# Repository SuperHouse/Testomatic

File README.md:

Testomatic PCB Test Jig System
==============================

Copyright 2024-2026 SuperHouse Automation Pty Ltd  [www.superhouse.tv]()

Testomatic is an open-source PCB test jig system with several goals:

1. Minimise reinvention when creating a test jig for a new **Device
Under Test (DUT)**.
2. Provide enough built-in I/O to **make the majority of tests easy**, with
expandability to **make harder tests possible**.
3. Allow the chassis to be quickly reused for multiple DUTs, with
each DUT having its own **Test Module**.
4. Integration with an **external test management / logging platform** for centralised storage of test results from one or more testers.

Testomatic is based around a Raspberry Pi, with a special PCB to provide additional I/O and protect the Pi from faults that may occur on the DUT. It uses removable Test Modules that provide the mechanical and electrical connection to each specific DUT. Currently we're using a simple Python testrunner script which has support for definition of multiple target boards, and can be controlled via the touchscreen using a control panel created using Node-RED Dashboard v2.

This is definitely a work in progress and the design is rapidly
developing. Most development and discussion of this project has taken
place on [SuperHouseTV livestreams](https://www.youtube.com/superhousetv) on YouTube, and on the [SuperHouse
Discord](https://www.superhouse.tv/discord/).

For an overview of how the project came to be and the design goals, see this 
presentation from Everything Open 2026:

The new v2 system is still in development and uses a vertically-mounted PCB with a card edge connector for bridging between the Raspberry Pi and the Test Module:

The v2.3 **Testomatic PCB**:

The **Testomatic PCB** fits into a laser-cut chassis with various other
parts:

**Test Modules** are built around a **Test Pin Carrier Board (TPCB)** which
uses a card edge connector commonly used for PCI to pass signals
between the Testomatic system and the test pins:

A reference design for the TPCB has been created as a starting point for making DUT-specific versions.

## Features
* 56 GPIOs grouped as 7 blocks, each with 8 pins.
* Each GPIO block can be configured for 3.3V or 5V I/O.
* Each GPIO pin can be digital input, digital output, 12-bit ADC, or 12-bit DAC.
* 4-port USB hub with all 4 ports passed up to the test module.
* SPI and I2C passed up to test module.
* Pi HAT EEPROM on Testomatic PCB for compliance with HAT automatic configuration.
* I2C EEPROM can be placed on Test Module to allow Testomatic to automatically identify which module is loaded.
* 5V power supply dedicated to Raspberry Pi independently of the DUT.
* 5V power supply with current sensing dedicated to DUT.
* 3V3 power supply with current sensing dedicated to DUT.
* VIN is passed to DUT with current sensing.
* Independent relay control of all 3 power rails to DUT.
* 1024 x 600 capacitive touchscreen.
* USB hub mounted in chassis for external connection of receipt printer, barcode scanner, keyboard, etc.
* Support for a 32-24 pixel thermal camera that can be mounted externally for capturing thermal images of the DUT.
* Support for an external button, such as a foot switch for control of test start.

## I/O Modules

Each block of 8 I/O pins is exposed on an I/O Module header, in 2mm pitch DIP format. This allows the use of different I/O modules to suit your needs. A generic I/O Module has been designed based on the AD5593R I2C I/O expander chip. Any pin on this module can be configured to be a digital input or output, analog input, or analog output.

Details of the module are available at [github.com/SuperHouse/IOMOD](https://github.com/SuperHouse/IOMOD)

The plan is to create other modules with different capabilities if required.

## Expansion
Simple tests can be done with the included I/O pins, but many DUTs will require more specific connections. Because the Test Module has SPI, I2C, and USB available, you can build your own custom circuitry directly into the Test Pin Carrier Board. This could include:

* USB-to-Serial converters
* CAN bus interfaces
* RS485 interfaces
* Dummy loads (either onboard or external)
* Light sensors
* Signal generators
* Programmable power supplies

To simplify this process for common tests, we have begun creating small modules that can be added quickly to the design of your Test Pin Carrier Board to save you doing this yourself. These modules include:

 * [USB-to-Serial / ESPFlasher](https://github.com/SuperHouse/ESPFMOD) (complete)
 * [CAN bus](https://github.com/SuperHouse/CANMOD) (complete)
 * [UPDI Programmer / Serial Module](https://github.com/SuperHouse/UPDIMOD)] (complete)

## LED Testing

Instead of relying on visual confirmation by an operator, Testomatic can use light sensors to 
validate correct operation of LEDs. These sensors can detect not only the level of illumination, 
but also the intensity at different wavelengths to verify that the correct colour of LED has 
been placed.

The "ColourSensor" directory contains Fusion design files and STLs for 30mm-long shrouds for 
mounting a VEML3328SL colour sensor, which in turn can be connected via I2C to the Testomatic. 

Designs are provided to suit 0603 LEDs in both straight and lateral orientations, and 3mm and 
5mm PTH LEDs.

The VEML3328SL can be carefully hand-soldered to the ends of thin wires connected to a JST-SH 
1mm connector for compatibility with Qwiic and Stemma, including breakout boards and multiplexers.

The VEML3328SL has a fixed I2C address of 0x10 so a common approach is to use a TCA9548A or 
PCA9546A I2C multiplexer to allow multiple colour sensors to be used.

## Testomatic Circuit Board Register

A closely related project is the Testomatic Circuit Board Register, which is software that 
provides a central location for storing production and testing data related to printed 
circuit board assembly (PCBA) services.

You can use Testomatic without the Register, and you can use the Register without Testomatic, 
but they are being developed in parallel with the intention that they complement each other 
and integrate smoothly.

Lean more about the Register at [github.com/SuperHouse/register](https://github.com/SuperHouse/register).

## Installation
Schematic and PCB were created in Fusion360 and exported as EAGLE format,
which can be imported back into Fusion360 or various other packages including KiCAD.

## Terminology
Chassis: A general purpose test jig that can execute tests.

Design: The abstract design of a type of printed circuit board, including the product name, SKU, schematic, PCB layout, bill of materials, and other production data.

Device: An assembled circuit board that is a concrete instantiation of a Design with an identifier such as a serial number that allows it to be unambiguously differentiated from other Devices of the same Design.

Device Under Test / DUT: When a Device is fitted into a Test Module in a Chassis so that it can be tested, it can be referred to as the Device Under Test.

Test Module: Hardware shim that fits into a Chassis and provides connections to a specific DUT.

Test Item: An abstract definition of an action that can be performed while testing a DUT, such as measurign a power rail, or sending a signal to it.

Test Step: An instantiation of a Test Item with specific configuration details such as which power rail to measure, or which I/O pin to use for sending a signal. Test Steps are executed automatically during the process of testing a DUT.

Manual Check: One step that is executed manually during the process of testing a DUT.

Test Suite: A collection of Test Items and Manual Checks that constitutes the steps required to test a DUT.

Test Run: One execution of a Test Suite against a Device Under Test.

Test Output: The data collected during a Test Run, with values and outcomes that are specific to that Device.

Test Result: Pass/Fail/Abort/Error. Pass: all Test Steps executed within required parameters. Fail: Test Suite was completed, but one or more Test Steps were outside required parameters. Abort: Test Suite was not completed because a Test Step caused the process to abort. Error: Test Suite was not completed because an environmental problem prevented execution.

Register: Software system that stores definitions of Designs, Test Items, and Test Suites, along with production data and Test Results related to Devices.

Test Suite Definition: A JSON file that contains the Test Steps and Manual Checks of a Test Suite.

Test Suite Package: A Test Suite Definition together with the additional artifacts it references and requires for execution, such as firmware binaries, whether delivered as a single archive or assembled from multiple sources such as separate API fetches.

Test Runner: Software that runs on the Chassis to load a Test Suite, execute its Test Steps against a Device, and report the resulting Test Results.

## Credits
Designed by Jonathan Oxer <jon@oxer.com.au> with the assistance of many members of the SuperHouse Discord.

## Distribution
The specific terms of distribution of this project are governed by the
license referenced below.

## License
Licensed under the TAPR Open Hardware License (www.tapr.org/OHL).
The "license" folder within this repository also contains a copy of
this license in plain text format.

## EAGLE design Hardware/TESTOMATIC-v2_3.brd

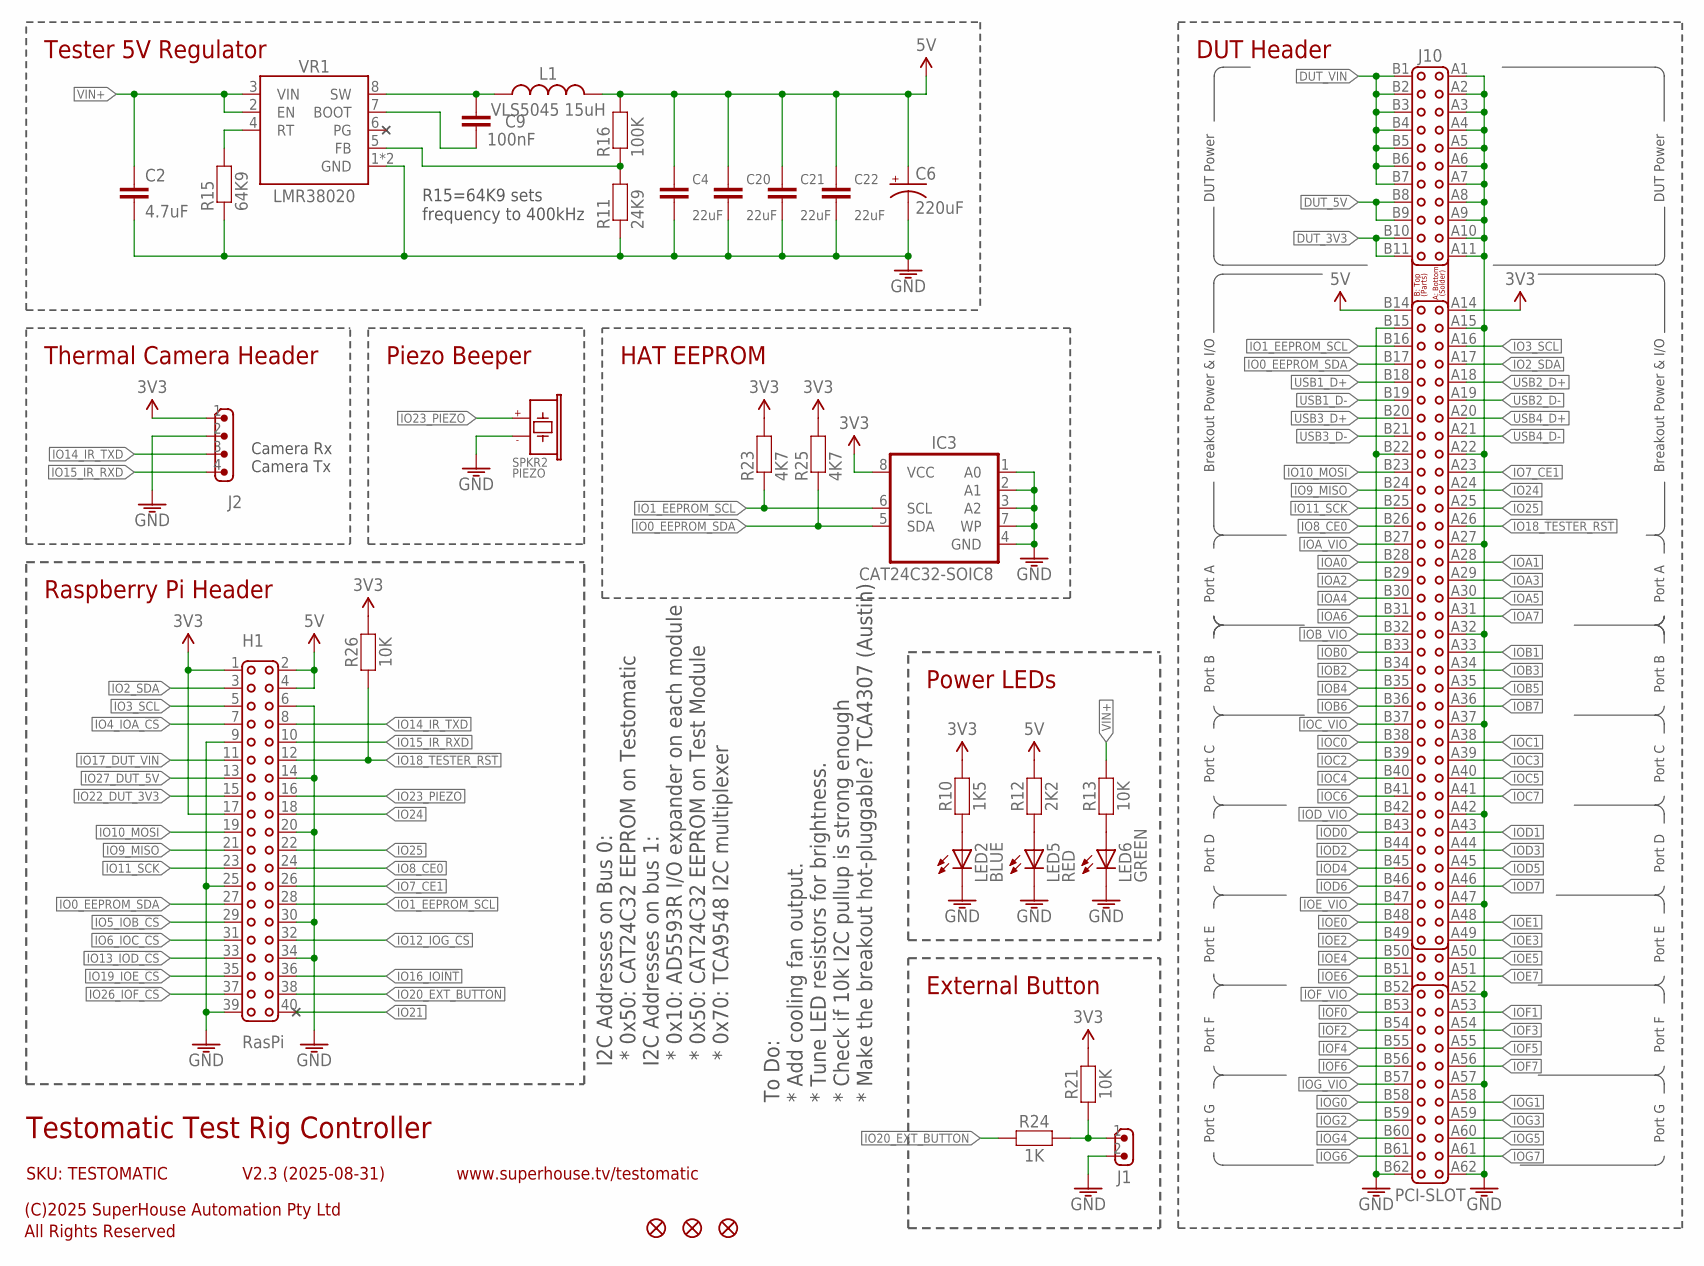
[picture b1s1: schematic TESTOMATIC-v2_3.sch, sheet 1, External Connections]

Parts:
C2: 4.7uF; C1206
C4, C20, C21, C22: 22uF; C0805
C6: 220uF; PANASONIC_G
C9: 100nF; C0603
FID1, FID2, FID3: FIDUCIAL1X2.5; FIDUCIAL-1X2.5
H1: RasPi; 2X20-P
IC3: CAT24C32-SOIC8; SOIC8
J1: M02-B2B-XH; JST-B2B-XH-A
J2: M04-B4B-XH; JST-B4B-XH-A
J10: PCI-SLOT
L1: VLS5045 15uH; INDUCTOR-5045
LED2: BLUE; LED-0603
LED5: RED; LED-0603
LED6: GREEN; LED-0603
R10: 1K5; R0603
R11: 24K9; R0603
R12: 2K2; R0603
R13, R21, R26: 10K; R0603
R15: 64K9; R0603
R16: 100K; R0603
R23, R25: 4K7; R0603
R24: 1K; R0603
SPKR2: PIEZO; PIEZO-9.6X9.6-SMT
VR1: LMR38020; HSOIC8

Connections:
3.3V: H1.1, H1.17, IC3.8 (VCC), J2.1, J10.A14, R10.2, R21.2, R23.2, R25.2, R26.2; also elsewhere on the board
5V: C4.1, C6.+, C20.1, C21.1, C22.1, H1.2, H1.4, J10.B14, L1.2, R12.2, R16.2; also elsewhere on the board
DUT_3V3: J10.B10, J10.B11; also elsewhere on the board
DUT_5V: J10.B8, J10.B9; also elsewhere on the board
DUT_VIN: J10.B1, J10.B2, J10.B3, J10.B4, J10.B5, J10.B6, J10.B7; also elsewhere on the board
GND: C2.2, C4.2, C6.-, C20.2, C21.2, C22.2, H1.6, H1.9, H1.14, H1.20, H1.25, H1.30, H1.34, H1.39, IC3.1 (A0), IC3.2 (A1), IC3.3 (A2), IC3.4 (GND), IC3.7 (WP), J1.2, J2.2, J10.A1, J10.A2, J10.A3, J10.A4, J10.A5, J10.A6, J10.A7, J10.A8, J10.A9, J10.A10, J10.A11, J10.A15, J10.A22, J10.A27, J10.A32, J10.A37, J10.A42, J10.A47, J10.A52, J10.A57, J10.A62, J10.B15, J10.B22, J10.B62, LED2.C, LED5.C, LED6.C, R11.1, R15.1, SPKR2.2 (-), VR1.1 (GND), VR1.TGND (GND); also elsewhere on the board
IO0_EEPROM_SDA: H1.27, IC3.5 (SDA), J10.B17, R25.1
IO1_EEPROM_SCL: H1.28, IC3.6 (SCL), J10.B16, R23.1
IO2_SDA: H1.3, J10.A17; also elsewhere on the board
IO3_SCL: H1.5, J10.A16; also elsewhere on the board
IO4_IOA_!CS: H1.7; also elsewhere on the board
IO5_IOB_!CS: H1.29; also elsewhere on the board
IO6_IOC_!CS: H1.31; also elsewhere on the board
IO7_CE1: H1.26, J10.A23
IO8_CE0: H1.24, J10.B26
IO9_MISO: H1.21, J10.B24; also elsewhere on the board
IO10_MOSI: H1.19, J10.B23; also elsewhere on the board
IO11_SCK: H1.23, J10.B25; also elsewhere on the board
IO12_IOG_!CS: H1.32; also elsewhere on the board
IO13_IOD_!CS: H1.33; also elsewhere on the board
IO14_IR_TXD: H1.8, J2.3
IO15_IR_RXD: H1.10, J2.4
IO16_IO!INT: H1.36; also elsewhere on the board
IO17_DUT_VIN: H1.11; also elsewhere on the board
IO18_!TESTER_RST: H1.12, J10.A26, R26.1; also elsewhere on the board
IO19_IOE_!CS: H1.35; also elsewhere on the board
IO20_EXT_BUTTON: H1.38, R24.1
IO21: H1.40
IO22_DUT_3V3: H1.15; also elsewhere on the board
IO23_PIEZO: H1.16, SPKR2.1 (+)
IO24: H1.18, J10.A24
IO25: H1.22, J10.A25
IO26_IOF_!CS: H1.37; also elsewhere on the board
IO27_DUT_5V: H1.13; also elsewhere on the board
IOA0: J10.B28; also elsewhere on the board
IOA1: J10.A28; also elsewhere on the board
IOA2: J10.B29; also elsewhere on the board
IOA3: J10.A29; also elsewhere on the board
IOA4: J10.B30; also elsewhere on the board
IOA5: J10.A30; also elsewhere on the board
IOA6: J10.B31; also elsewhere on the board
IOA7: J10.A31; also elsewhere on the board
IOA_VIO: J10.B27; also elsewhere on the board
IOB0: J10.B33; also elsewhere on the board
IOB1: J10.A33; also elsewhere on the board
IOB2: J10.B34; also elsewhere on the board
IOB3: J10.A34; also elsewhere on the board
IOB4: J10.B35; also elsewhere on the board
IOB5: J10.A35; also elsewhere on the board
IOB6: J10.B36; also elsewhere on the board
IOB7: J10.A36; also elsewhere on the board
IOB_VIO: J10.B32; also elsewhere on the board
IOC0: J10.B38; also elsewhere on the board
IOC1: J10.A38; also elsewhere on the board
IOC2: J10.B39; also elsewhere on the board
IOC3: J10.A39; also elsewhere on the board
IOC4: J10.B40; also elsewhere on the board
IOC5: J10.A40; also elsewhere on the board
IOC6: J10.B41; also elsewhere on the board
IOC7: J10.A41; also elsewhere on the board
IOC_VIO: J10.B37; also elsewhere on the board
IOD0: J10.B43; also elsewhere on the board
IOD1: J10.A43; also elsewhere on the board
IOD2: J10.B44; also elsewhere on the board
IOD3: J10.A44; also elsewhere on the board
IOD4: J10.B45; also elsewhere on the board
IOD5: J10.A45; also elsewhere on the board
IOD6: J10.B46; also elsewhere on the board
IOD7: J10.A46; also elsewhere on the board
IOD_VIO: J10.B42; also elsewhere on the board
IOE0: J10.B48; also elsewhere on the board
IOE1: J10.A48; also elsewhere on the board
IOE2: J10.B49; also elsewhere on the board
IOE3: J10.A49; also elsewhere on the board
IOE4: J10.B50; also elsewhere on the board
IOE5: J10.A50; also elsewhere on the board
IOE6: J10.B51; also elsewhere on the board
IOE7: J10.A51; also elsewhere on the board
IOE_VIO: J10.B47; also elsewhere on the board
IOF0: J10.B53; also elsewhere on the board
IOF1: J10.A53; also elsewhere on the board
IOF2: J10.B54; also elsewhere on the board
IOF3: J10.A54; also elsewhere on the board
IOF4: J10.B55; also elsewhere on the board
IOF5: J10.A55; also elsewhere on the board
IOF6: J10.B56; also elsewhere on the board
IOF7: J10.A56; also elsewhere on the board
IOF_VIO: J10.B52; also elsewhere on the board
IOG0: J10.B58; also elsewhere on the board
IOG1: J10.A58; also elsewhere on the board
IOG2: J10.B59; also elsewhere on the board
IOG3: J10.A59; also elsewhere on the board
IOG4: J10.B60; also elsewhere on the board
IOG5: J10.A60; also elsewhere on the board
IOG6: J10.B61; also elsewhere on the board
IOG7: J10.A61; also elsewhere on the board
IOG_VIO: J10.B57; also elsewhere on the board
unnamed: LED2.A, R10.1
unnamed: C9.1, L1.1, VR1.8 (SW)
unnamed: LED5.A, R12.1
unnamed: LED6.A, R13.1
unnamed: J1.1, R21.1, R24.2
unnamed: R15.2, VR1.4 (RT)
unnamed: R11.2, R16.1, VR1.5 (FB)
unnamed: C9.2, VR1.7 (BOOT)
PG: VR1.6 (PG); also elsewhere on the board
USB1_D+: J10.B18; also elsewhere on the board
USB1_D-: J10.B19; also elsewhere on the board
USB2_D+: J10.A18; also elsewhere on the board
USB2_D-: J10.A19; also elsewhere on the board
USB3_D+: J10.B20; also elsewhere on the board
USB3_D-: J10.B21; also elsewhere on the board
USB4_D+: J10.A20; also elsewhere on the board
USB4_D-: J10.A21; also elsewhere on the board
VIN+: C2.1, R13.2, VR1.2 (EN), VR1.3 (VIN); also elsewhere on the board

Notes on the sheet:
Testomatic Test Rig Controller
V2.3 (2025-08-31)
SKU: TESTOMATIC
(C)2025 SuperHouse Automation Pty Ltd
All Rights Reserved
www.superhouse.tv/testomatic
Tester 5V Regulator
R15=64K9 sets frequency to 400kHz
To Do: * Add cooling fan output. * Tune LED resistors for brightness. * Check if 10k I2C pullup is strong enough * Make the breakout hot-pluggable? TCA4307 (Austin)
Raspberry Pi Header
Thermal Camera Header
Camera Rx
Camera Tx
DUT Header
Piezo Beeper
DUT Power
Breakout Power & I/O
Port D
Power LEDs
External Button
HAT EEPROM
Port E
Port F
Port G
Port C
Port B
Port A
I2C Addresses on Bus 0: * 0x50: CAT24C32 EEPROM on Testomatic I2C Addresses on bus 1: * 0x10: AD5593R I/O expander on each module * 0x50: CAT24C32 EEPROM on Test Module * 0x70: TCA9548 I2C multiplexer

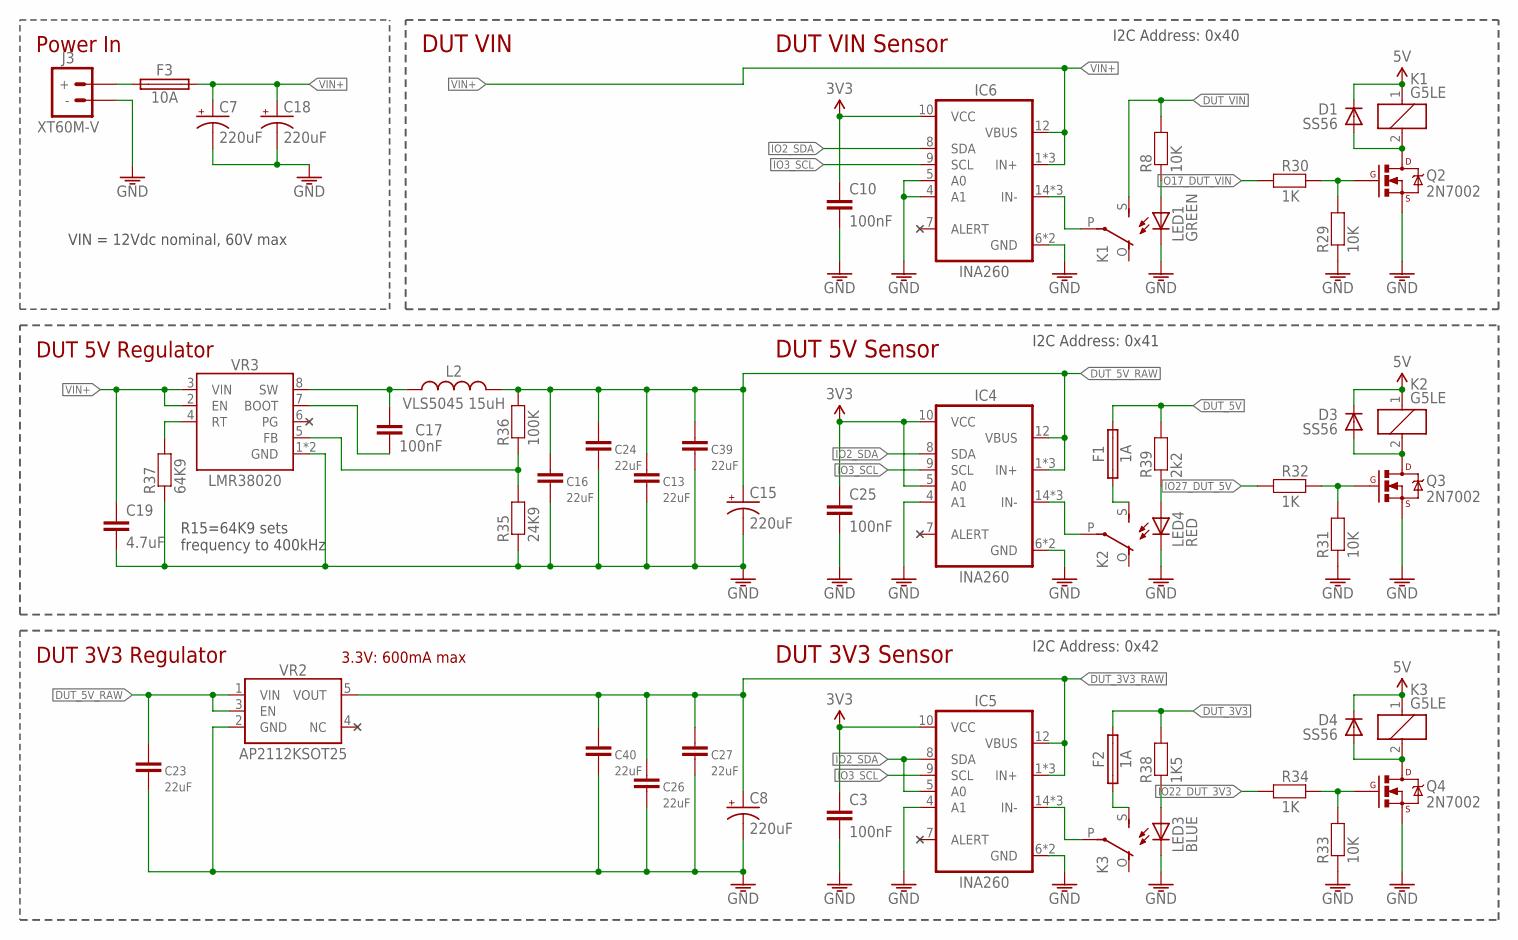
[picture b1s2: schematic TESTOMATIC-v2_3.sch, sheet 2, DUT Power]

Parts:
C3, C10, C17, C25: 100nF; C0603
C7, C8, C15, C18: 220uF; PANASONIC_G
C13, C16, C23, C24, C26, C27, C39, C40: 22uF; C0805
C19: 4.7uF; C1206
D1, D3, D4: SS56; SMA-DIODE
F1, F2: 1A; 1206
F3: 10A; MCCQ-122
IC4, IC5, IC6: INA260; TSSOP-16
J3: XT60M-V; XT60PW-M-V
K1, K2, K3: G5LE
L2: VLS5045 15uH; INDUCTOR-5045
LED1: GREEN; LED-0603
LED3: BLUE; LED-0603
LED4: RED; LED-0603
Q2, Q3, Q4: 2N7002; SOT23-3
R8, R29, R31, R33: 10K; R0603
R30, R32, R34: 1K; R0603
R35: 24K9; R0603
R36: 100K; R0603
R37: 64K9; R0603
R38: 1K5; R0603
R39: 2k2; R0603
VR2: AP2112KSOT25; SOT23-5
VR3: LMR38020; HSOIC8

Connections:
3.3V: C3.1, C10.1, C25.1, IC4.5 (A0), IC4.10 (VCC), IC5.10 (VCC), IC6.10 (VCC); also elsewhere on the board
5V: D1.C, D3.C, D4.C, K1.1, K2.1, K3.1; also elsewhere on the board
DUT_3V3: F2.2, R38.2; also elsewhere on the board
DUT_3V3_RAW: C8.+, C26.1, C27.1, C40.1, IC5.1 (IN+), IC5.2 (IN+), IC5.3 (IN+), IC5.12 (VBUS), VR2.5 (VOUT)
DUT_5V: F1.2, R39.2; also elsewhere on the board
DUT_5V_RAW: C13.1, C15.+, C16.1, C23.1, C24.1, C39.1, IC4.1 (IN+), IC4.2 (IN+), IC4.3 (IN+), IC4.12 (VBUS), L2.2, R36.2, VR2.1 (VIN), VR2.3 (EN)
DUT_VIN: K1.S (NO), R8.2; also elsewhere on the board
GND: C3.2, C7.-, C8.-, C10.2, C13.2, C15.-, C16.2, C18.-, C19.2, C23.2, C24.2, C25.2, C26.2, C27.2, C39.2, C40.2, IC4.4 (A1), IC4.6 (GND), IC4.11 (GND), IC5.4 (A1), IC5.6 (GND), IC5.11 (GND), IC6.4 (A1), IC6.5 (A0), IC6.6 (GND), IC6.11 (GND), J3.-, LED1.C, LED3.C, LED4.C, Q2.2 (S), Q3.2 (S), Q4.2 (S), R29.1, R31.1, R33.1, R35.1, R37.1, VR2.2 (GND), VR3.1 (GND), VR3.TGND (GND); also elsewhere on the board
IO2_SDA: IC4.8 (SDA), IC5.5 (A0), IC5.8 (SDA), IC6.8 (SDA); also elsewhere on the board
IO3_SCL: IC4.9 (SCL), IC5.9 (SCL), IC6.9 (SCL); also elsewhere on the board
IO17_DUT_VIN: R30.1; also elsewhere on the board
IO22_DUT_3V3: R34.1; also elsewhere on the board
IO27_DUT_5V: R32.1; also elsewhere on the board
unnamed: F3.1, F3.2 (1), J3.+
unnamed: D4.A, K3.2, Q4.3 (D)
unnamed: IC4.14 (IN-), IC4.15 (IN-), IC4.16 (IN-), K2.P (COM)
unnamed: IC6.14 (IN-), IC6.15 (IN-), IC6.16 (IN-), K1.P (COM)
unnamed: D1.A, K1.2, Q2.3 (D)
unnamed: LED1.A, R8.1
unnamed: Q2.1 (G), R29.2, R30.2
unnamed: F2.1, K3.S (NO)
unnamed: F1.1, K2.S (NO)
unnamed: D3.A, K2.2, Q3.3 (D)
unnamed: Q3.1 (G), R31.2, R32.2
unnamed: Q4.1 (G), R33.2, R34.2
unnamed: IC5.14 (IN-), IC5.15 (IN-), IC5.16 (IN-), K3.P (COM)
unnamed: C17.1, L2.1, VR3.8 (SW)
unnamed: R37.2, VR3.4 (RT)
unnamed: R35.2, R36.1, VR3.5 (FB)
unnamed: C17.2, VR3.7 (BOOT)
unnamed: LED4.A, R39.1
unnamed: LED3.A, R38.1
PG: VR3.6 (PG); also elsewhere on the board
VIN+: C7.+, C18.+, C19.1, F3.3 (2), F3.4 (2), IC6.1 (IN+), IC6.2 (IN+), IC6.3 (IN+), IC6.12 (VBUS), VR3.2 (EN), VR3.3 (VIN); also elsewhere on the board

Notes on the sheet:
DUT VIN Sensor
I2C Address: 0x40
DUT 5V Sensor
I2C Address: 0x41
DUT 3V3 Sensor
I2C Address: 0x42
3.3V: 600mA max
DUT 3V3 Regulator
DUT 5V Regulator
R15=64K9 sets frequency to 400kHz
DUT VIN
VIN = 12Vdc nominal, 60V max
Power In

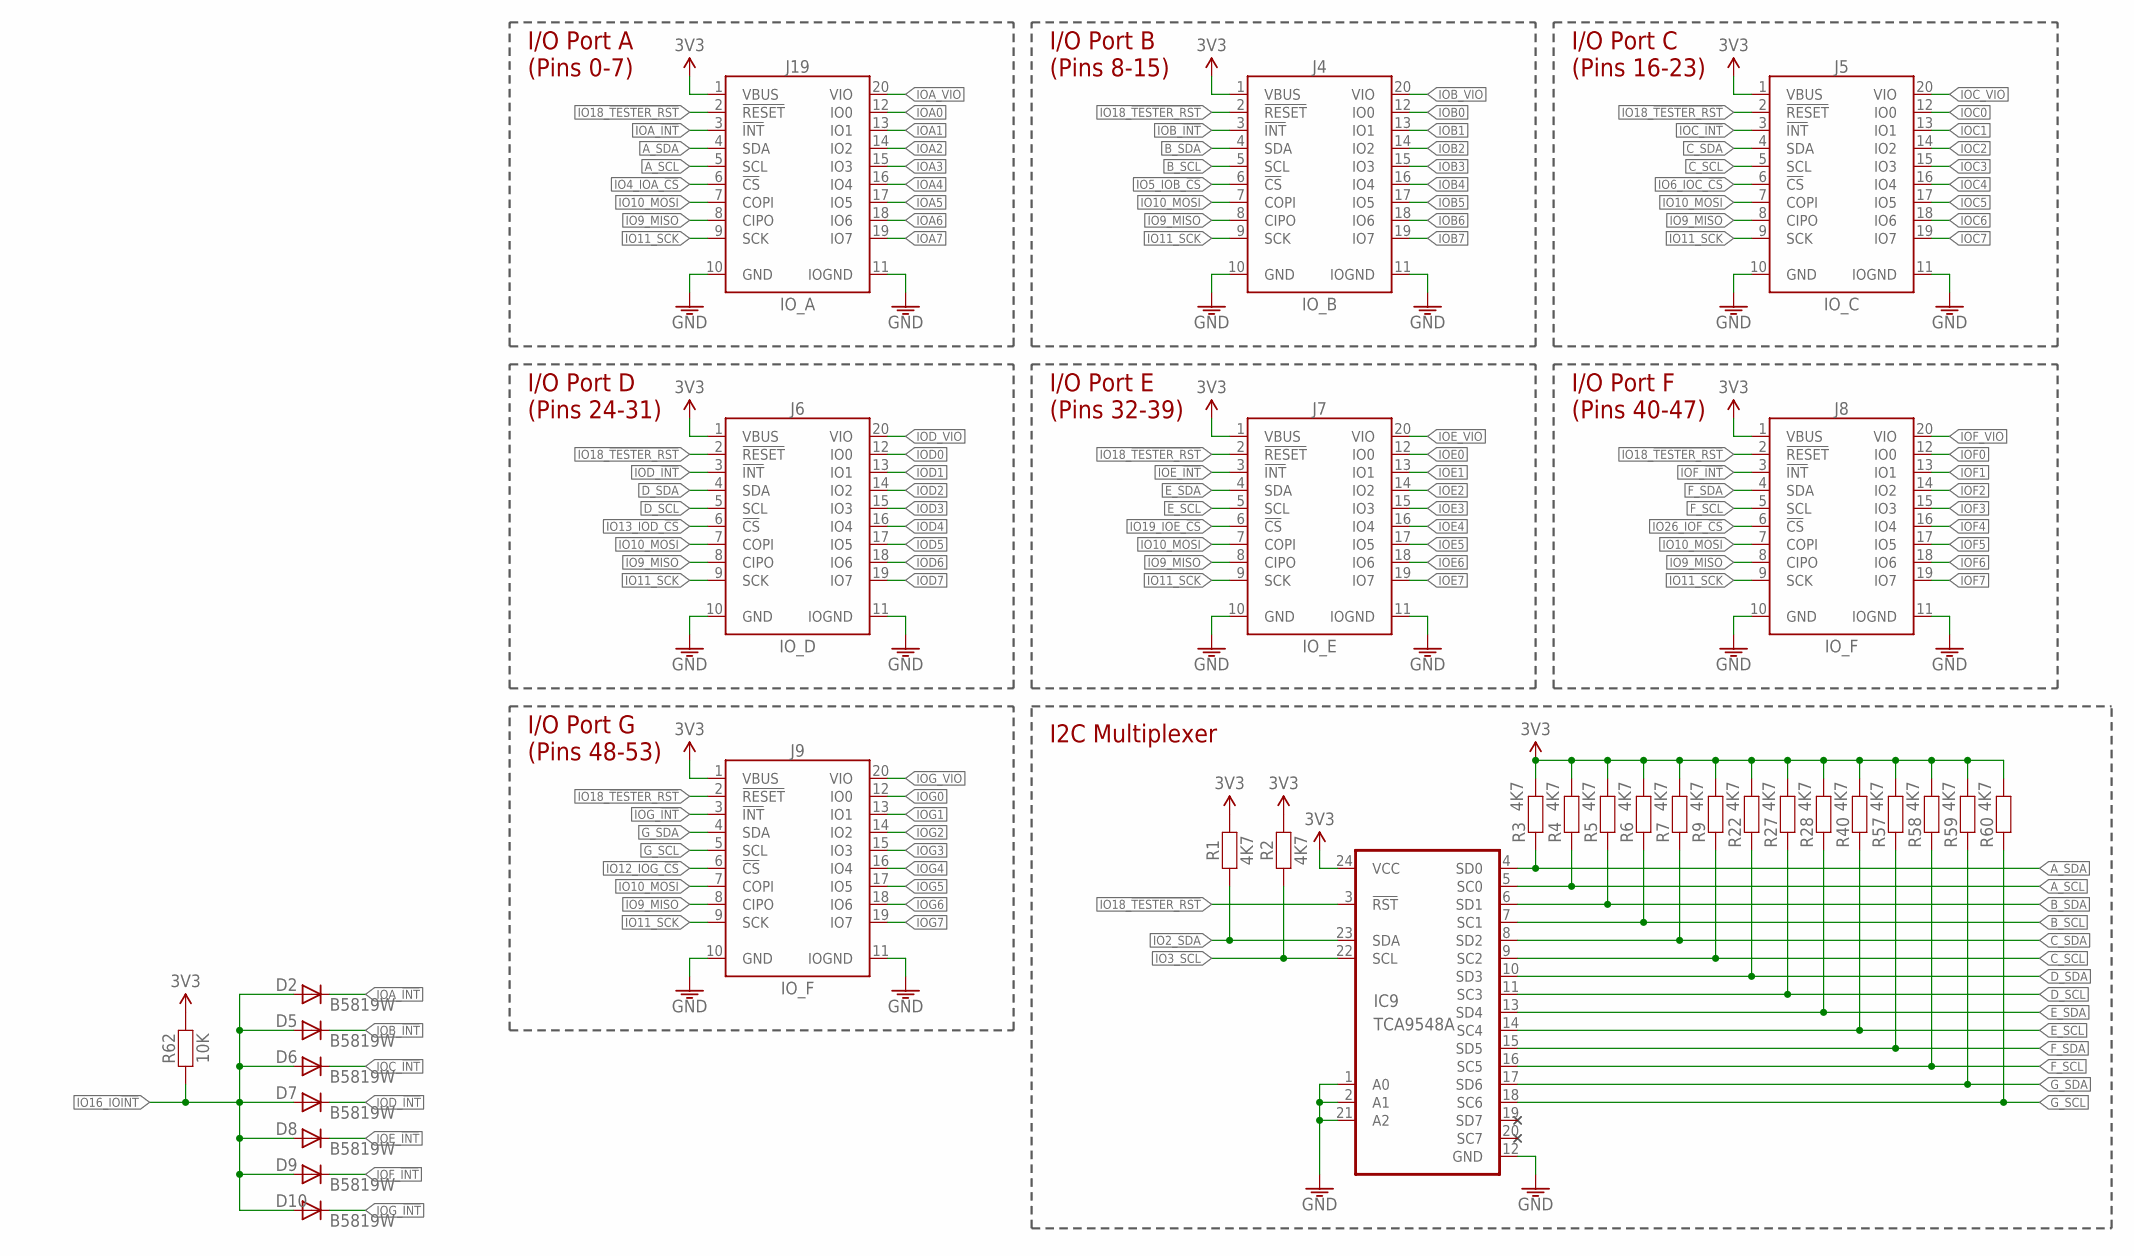
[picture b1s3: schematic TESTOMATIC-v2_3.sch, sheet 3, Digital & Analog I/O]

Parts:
D2, D5, D6, D7, D8, D9, D10: B5819W; SOD-123
IC9: TCA9548A; TSSOP24
J4: IO_B; IOMOD
J5: IO_C; IOMOD
J6: IO_D; IOMOD
J7: IO_E; IOMOD
J8, J9: IO_F; IOMOD
J19: IO_A; IOMOD
R1, R2, R3, R4, R5, R6, R7, R9, R22, R27, R28, R40, R57, R58, R59, R60: 4K7; R0603
R62: 10K; R0603

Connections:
3.3V: IC9.24 (VCC), J4.1 (VBUS), J5.1 (VBUS), J6.1 (VBUS), J7.1 (VBUS), J8.1 (VBUS), J9.1 (VBUS), J19.1 (VBUS), R1.2, R2.2, R3.2, R4.2, R5.2, R6.2, R7.2, R9.2, R22.2, R27.2, R28.2, R40.2, R57.2, R58.2, R59.2, R60.2, R62.2; also elsewhere on the board
A_SCL: IC9.5 (SC0), J19.5 (SCL), R4.1
A_SDA: IC9.4 (SD0), J19.4 (SDA), R3.1
B_SCL: IC9.7 (SC1), J4.5 (SCL), R6.1
B_SDA: IC9.6 (SD1), J4.4 (SDA), R5.1
C_SCL: IC9.9 (SC2), J5.5 (SCL), R9.1
C_SDA: IC9.8 (SD2), J5.4 (SDA), R7.1
D_SCL: IC9.11 (SC3), J6.5 (SCL), R27.1
D_SDA: IC9.10 (SD3), J6.4 (SDA), R22.1
E_SCL: IC9.14 (SC4), J7.5 (SCL), R40.1
E_SDA: IC9.13 (SD4), J7.4 (SDA), R28.1
F_SCL: IC9.16 (SC5), J8.5 (SCL), R58.1
F_SDA: IC9.15 (SD5), J8.4 (SDA), R57.1
GND: IC9.1 (A0), IC9.2 (A1), IC9.12 (GND), IC9.21 (A2), J4.10 (GND), J4.11 (IOGND), J5.10 (GND), J5.11 (IOGND), J6.10 (GND), J6.11 (IOGND), J7.10 (GND), J7.11 (IOGND), J8.10 (GND), J8.11 (IOGND), J9.10 (GND), J9.11 (IOGND), J19.10 (GND), J19.11 (IOGND); also elsewhere on the board
G_SCL: IC9.18 (SC6), J9.5 (SCL), R60.1
G_SDA: IC9.17 (SD6), J9.4 (SDA), R59.1
IO2_SDA: IC9.23 (SDA), R1.1; also elsewhere on the board
IO3_SCL: IC9.22 (SCL), R2.1; also elsewhere on the board
IO4_IOA_!CS: J19.6 (!CS); also elsewhere on the board
IO5_IOB_!CS: J4.6 (!CS); also elsewhere on the board
IO6_IOC_!CS: J5.6 (!CS); also elsewhere on the board
IO9_MISO: J4.8 (CIPO), J5.8 (CIPO), J6.8 (CIPO), J7.8 (CIPO), J8.8 (CIPO), J9.8 (CIPO), J19.8 (CIPO); also elsewhere on the board
IO10_MOSI: J4.7 (COPI), J5.7 (COPI), J6.7 (COPI), J7.7 (COPI), J8.7 (COPI), J9.7 (COPI), J19.7 (COPI); also elsewhere on the board
IO11_SCK: J4.9 (SCK), J5.9 (SCK), J6.9 (SCK), J7.9 (SCK), J8.9 (SCK), J9.9 (SCK), J19.9 (SCK); also elsewhere on the board
IO12_IOG_!CS: J9.6 (!CS); also elsewhere on the board
IO13_IOD_!CS: J6.6 (!CS); also elsewhere on the board
IO16_IO!INT: D2.2 (A), D5.2 (A), D6.2 (A), D7.2 (A), D8.2 (A), D9.2 (A), D10.2 (A), R62.1; also elsewhere on the board
IO18_!TESTER_RST: IC9.3 (!RST), J4.2 (!RESET), J5.2 (!RESET), J6.2 (!RESET), J7.2 (!RESET), J8.2 (!RESET), J9.2 (!RESET), J19.2 (!RESET); also elsewhere on the board
IO19_IOE_!CS: J7.6 (!CS); also elsewhere on the board
IO26_IOF_!CS: J8.6 (!CS); also elsewhere on the board
IOA0: J19.12 (IO0); also elsewhere on the board
IOA1: J19.13 (IO1); also elsewhere on the board
IOA2: J19.14 (IO2); also elsewhere on the board
IOA3: J19.15 (IO3); also elsewhere on the board
IOA4: J19.16 (IO4); also elsewhere on the board
IOA5: J19.17 (IO5); also elsewhere on the board
IOA6: J19.18 (IO6); also elsewhere on the board
IOA7: J19.19 (IO7); also elsewhere on the board
IOA_!INT: D2.1 (C), J19.3 (!INT)
IOA_VIO: J19.20 (VIO); also elsewhere on the board
IOB0: J4.12 (IO0); also elsewhere on the board
IOB1: J4.13 (IO1); also elsewhere on the board
IOB2: J4.14 (IO2); also elsewhere on the board
IOB3: J4.15 (IO3); also elsewhere on the board
IOB4: J4.16 (IO4); also elsewhere on the board
IOB5: J4.17 (IO5); also elsewhere on the board
IOB6: J4.18 (IO6); also elsewhere on the board
IOB7: J4.19 (IO7); also elsewhere on the board
IOB_!INT: D5.1 (C), J4.3 (!INT)
IOB_VIO: J4.20 (VIO); also elsewhere on the board
IOC0: J5.12 (IO0); also elsewhere on the board
IOC1: J5.13 (IO1); also elsewhere on the board
IOC2: J5.14 (IO2); also elsewhere on the board
IOC3: J5.15 (IO3); also elsewhere on the board
IOC4: J5.16 (IO4); also elsewhere on the board
IOC5: J5.17 (IO5); also elsewhere on the board
IOC6: J5.18 (IO6); also elsewhere on the board
IOC7: J5.19 (IO7); also elsewhere on the board
IOC_!INT: D6.1 (C), J5.3 (!INT)
IOC_VIO: J5.20 (VIO); also elsewhere on the board
IOD0: J6.12 (IO0); also elsewhere on the board
IOD1: J6.13 (IO1); also elsewhere on the board
IOD2: J6.14 (IO2); also elsewhere on the board
IOD3: J6.15 (IO3); also elsewhere on the board
IOD4: J6.16 (IO4); also elsewhere on the board
IOD5: J6.17 (IO5); also elsewhere on the board
IOD6: J6.18 (IO6); also elsewhere on the board
IOD7: J6.19 (IO7); also elsewhere on the board
IOD_!INT: D7.1 (C), J6.3 (!INT)
IOD_VIO: J6.20 (VIO); also elsewhere on the board
IOE0: J7.12 (IO0); also elsewhere on the board
IOE1: J7.13 (IO1); also elsewhere on the board
IOE2: J7.14 (IO2); also elsewhere on the board
IOE3: J7.15 (IO3); also elsewhere on the board
IOE4: J7.16 (IO4); also elsewhere on the board
IOE5: J7.17 (IO5); also elsewhere on the board
IOE6: J7.18 (IO6); also elsewhere on the board
IOE7: J7.19 (IO7); also elsewhere on the board
IOE_!INT: D8.1 (C), J7.3 (!INT)
IOE_VIO: J7.20 (VIO); also elsewhere on the board
IOF0: J8.12 (IO0); also elsewhere on the board
IOF1: J8.13 (IO1); also elsewhere on the board
IOF2: J8.14 (IO2); also elsewhere on the board
IOF3: J8.15 (IO3); also elsewhere on the board
IOF4: J8.16 (IO4); also elsewhere on the board
IOF5: J8.17 (IO5); also elsewhere on the board
IOF6: J8.18 (IO6); also elsewhere on the board
IOF7: J8.19 (IO7); also elsewhere on the board
IOF_!INT: D9.1 (C), J8.3 (!INT)
IOF_VIO: J8.20 (VIO); also elsewhere on the board
IOG0: J9.12 (IO0); also elsewhere on the board
IOG1: J9.13 (IO1); also elsewhere on the board
IOG2: J9.14 (IO2); also elsewhere on the board
IOG3: J9.15 (IO3); also elsewhere on the board
IOG4: J9.16 (IO4); also elsewhere on the board
IOG5: J9.17 (IO5); also elsewhere on the board
IOG6: J9.18 (IO6); also elsewhere on the board
IOG7: J9.19 (IO7); also elsewhere on the board
IOG_!INT: D10.1 (C), J9.3 (!INT)
IOG_VIO: J9.20 (VIO); also elsewhere on the board

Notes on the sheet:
I/O Port A (Pins 0-7)
I2C Multiplexer
I/O Port B (Pins 8-15)
I/O Port C (Pins 16-23)
I/O Port D (Pins 24-31)
I/O Port E (Pins 32-39)
I/O Port F (Pins 40-47)
I/O Port G (Pins 48-53)

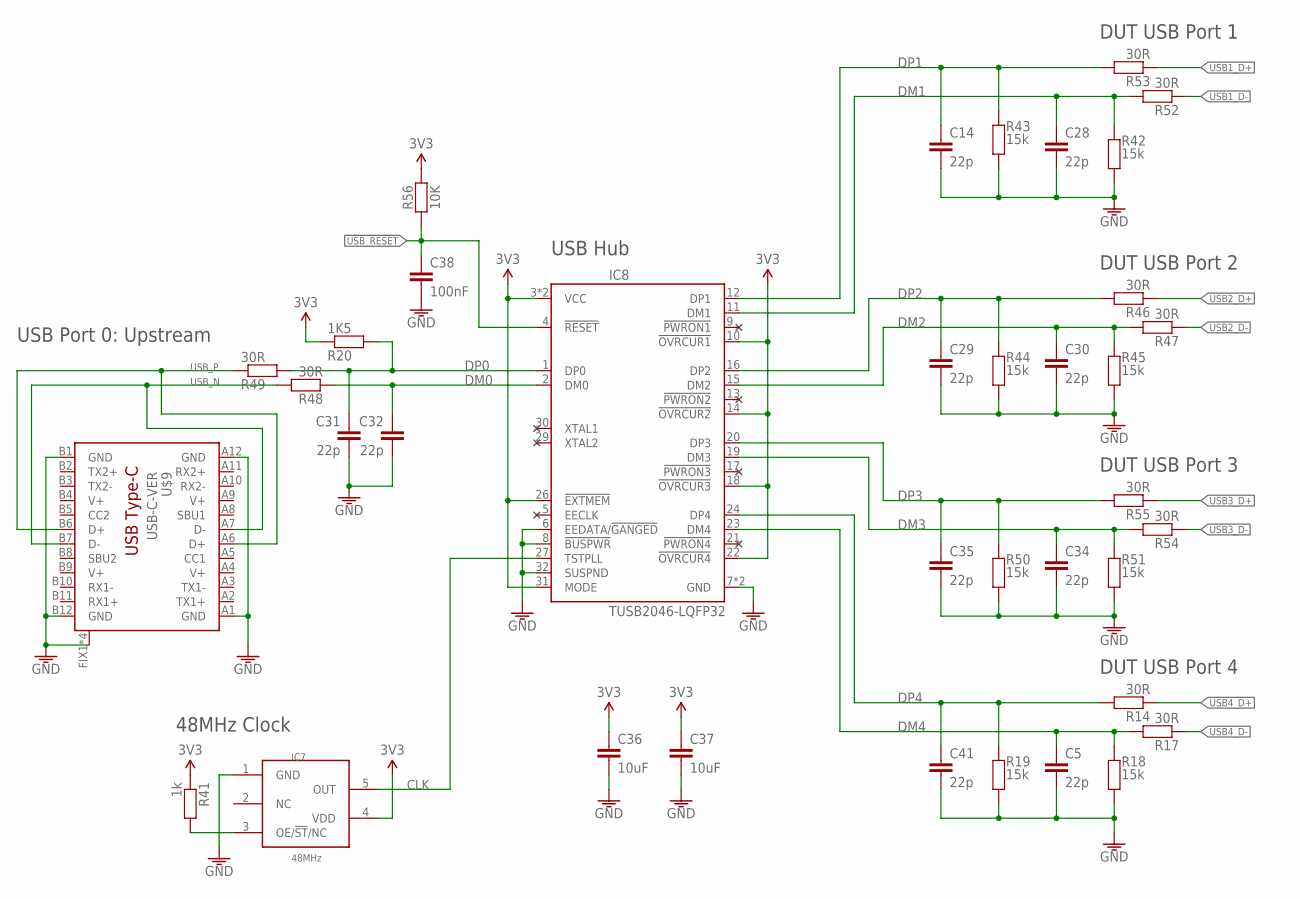
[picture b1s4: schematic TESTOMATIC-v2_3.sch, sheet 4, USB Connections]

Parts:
C5, C14, C28, C29, C30, C31, C32, C34, C35, C41: 22p; C0603
C36, C37: 10uF; C0805
C38: 100nF; C0603
IC7: 48MHz; SOT-23-5
IC8: TUSB2046-LQFP32; LQFP32
R14, R17, R46, R47, R48, R49, R52, R53, R54, R55: 30R; R0603
R18, R19, R42, R43, R44, R45, R50, R51: 15k; R0603
R20: 1K5; R0603
R41: 1k; R0603
R56: 10K; R0603
U$9: USB-C-VER; USB-C-VERT

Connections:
3.3V: C36.1, C37.1, IC7.4 (VDD), IC8.3 (VCC), IC8.10 (!OVRCUR1), IC8.14 (!OVRCUR2), IC8.18 (!OVRCUR3), IC8.22 (!OVRCUR4), IC8.25 (VCC), IC8.26 (!EXTMEM), IC8.31 (MODE), R20.1, R41.1, R56.2; also elsewhere on the board
!USB_RESET: C38.1, IC8.4 (!RESET), R56.1
CLK: IC7.5 (OUT), IC8.27 (TSTPLL)
DM0: C32.1, IC8.2 (DM0), R48.2
DM1: C28.1, IC8.11 (DM1), R42.1, R52.2
DM2: C30.1, IC8.15 (DM2), R45.1, R47.2
DM3: C34.1, IC8.19 (DM3), R51.1, R54.2
DM4: C5.1, IC8.23 (DM4), R17.2, R18.1
DP0: C31.1, IC8.1 (DP0), R20.2, R49.2
DP1: C14.1, IC8.12 (DP1), R43.1, R53.2
DP2: C29.1, IC8.16 (DP2), R44.1, R46.2
DP3: C35.1, IC8.20 (DP3), R50.1, R55.2
DP4: C41.1, IC8.24 (DP4), R14.2, R19.1
GND: C5.2, C14.2, C28.2, C29.2, C30.2, C31.2, C32.2, C34.2, C35.2, C36.2, C37.2, C38.2, C41.2, IC7.1 (GND), IC8.6 (EEDATA/!GANGED), IC8.7 (GND), IC8.8 (!BUSPWR), IC8.28 (GND), IC8.32 (SUSPND), R18.2, R19.2, R42.2, R43.2, R44.2, R45.2, R50.2, R51.2, U$9.A1 (GND), U$9.A12 (GND), U$9.B1 (GND), U$9.B12 (GND), U$9.FIX1 (CASE), U$9.FIX2 (CASE), U$9.FIX3 (CASE), U$9.FIX4 (CASE); also elsewhere on the board
unnamed: IC7.3 (OE/!ST!/NC), R41.2
USB1_D+: R53.1; also elsewhere on the board
USB1_D-: R52.1; also elsewhere on the board
USB2_D+: R46.1; also elsewhere on the board
USB2_D-: R47.1; also elsewhere on the board
USB3_D+: R55.1; also elsewhere on the board
USB3_D-: R54.1; also elsewhere on the board
USB4_D+: R14.1; also elsewhere on the board
USB4_D-: R17.1; also elsewhere on the board
USB_N: R48.1, U$9.A7 (D-), U$9.B7 (D-)
USB_P: R49.1, U$9.A6 (D+), U$9.B6 (D+)
V+: U$9.A4 (V+), U$9.A9 (V+), U$9.B4 (V+), U$9.B9 (V+)

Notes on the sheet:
DUT USB Port 1
DUT USB Port 2
DUT USB Port 3
USB Hub
USB Port 0: Upstream
48MHz Clock
DUT USB Port 4

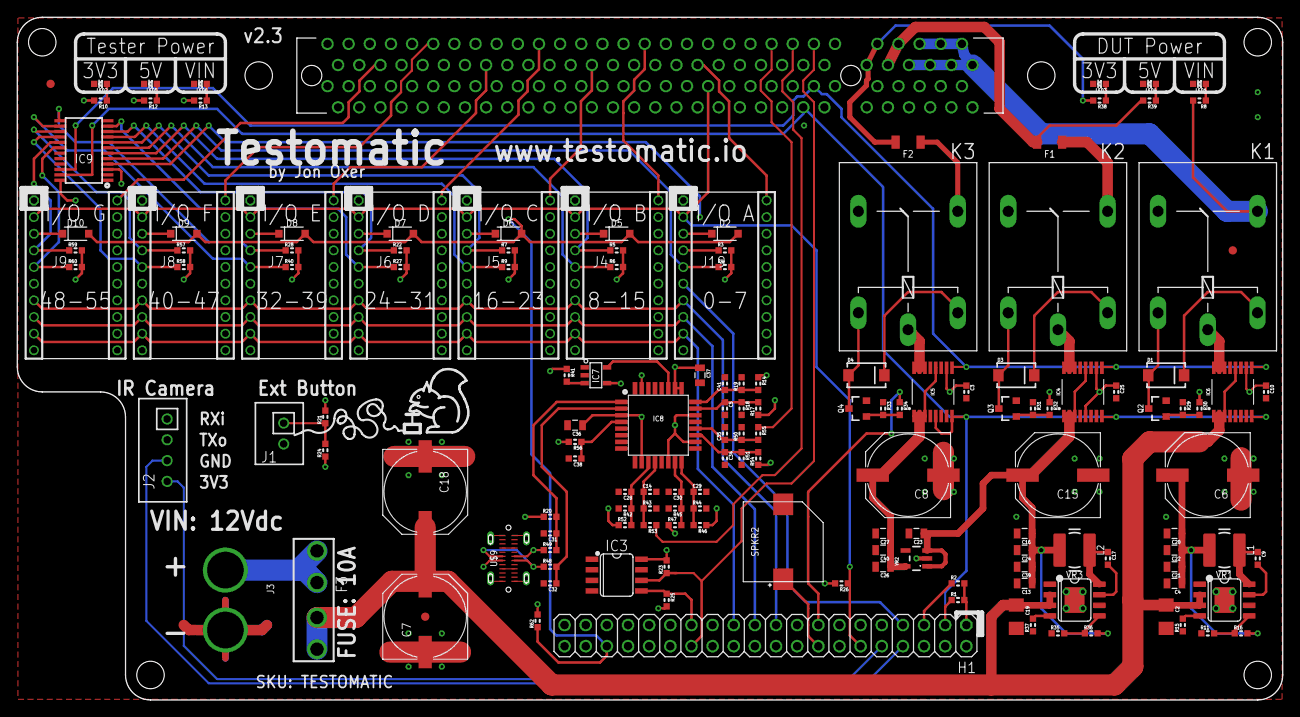
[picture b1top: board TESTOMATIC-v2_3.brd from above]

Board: 6 copper layers, 152.0 x 82.0 mm, 152 parts (0 on the bottom side), 172 nets.
